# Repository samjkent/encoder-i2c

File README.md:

# EAW0J 128 Absolute Encoders and LEDs

128 position encoders with LEDs to display state

Encoder input is read using an MCP23017, and LED state is set using an HT16K33

# Large 

128 LEDs in a ring around a single encoder, with a circumference of roughly 6cm

# Small

4 encoders with 32 LEDs per encoder. Requires 2 MCP23017 to provide enough inputs for the encoders.

# Example Application

Combined with [samjkent/stm32f4-midi-brain](https://github.com/samjkent/stm32f4-midi-brain) to create a MIDI controller

# Note

The encoder footprint used in these schematics contains a mistake where pins 9 and 10 switched. Software for the current hardware takes this into account.

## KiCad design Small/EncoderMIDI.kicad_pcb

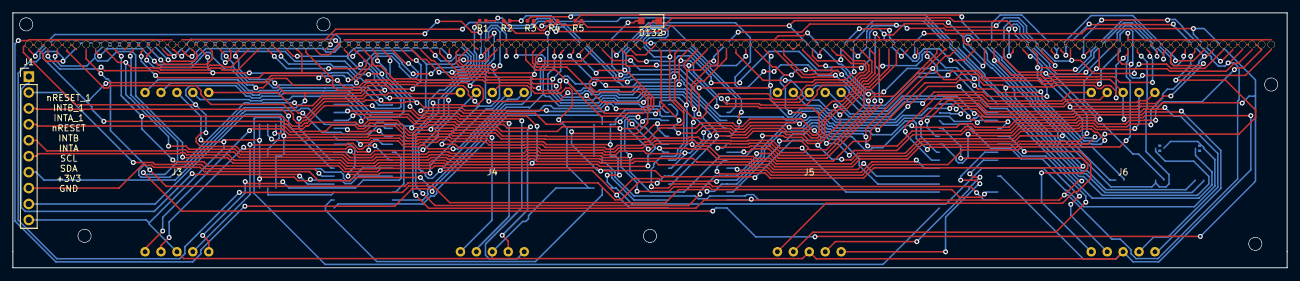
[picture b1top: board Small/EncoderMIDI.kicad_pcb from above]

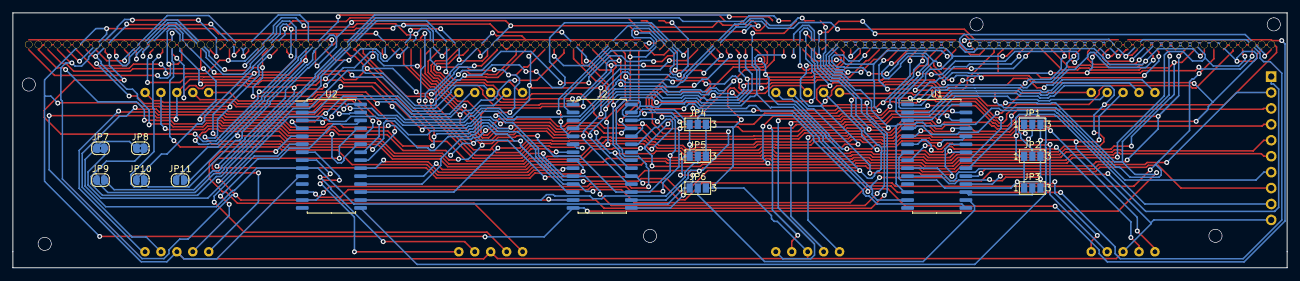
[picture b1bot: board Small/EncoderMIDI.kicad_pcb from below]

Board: 2 copper layers, 203.2 x 40.6 mm, 153 parts (14 on the bottom side), 58 nets.

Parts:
D1, D2, D3, D4, D5, D6, D7, D8, D9, D10, D11, D12, D13, D14, D15, D16, D17, D18, D19, D20, D21, D22, D23, D24, D25, D26, D27, D28, D29, D30, D31, D32, D34, D35, D36, D37, D38, D39, D40, D41, D42, D43, D44, D45, D46, D47, D48, D49, D50, D51, D52, D53, D54, D55, D56, D57, D58, D59, D60, D61, D62, D63, D64, D65, D67, D68, D69, D70, D71, D72, D73, D74, D75, D76, D77, D78, D79, D80, D81, D82, D83, D84, D85, D86, D87, D88, D89, D90, D91, D92, D93, D94, D95, D96, D97, D98, D100, D101, D102, D103, D104, D105, D106, D107, D108, D109, D110, D111, D112, D113, D114, D115, D116, D117, D118, D119, D120, D121, D122, D123, D124, D125, D126, D127, D128, D129, D130, D131: LED; LED_0603_1608Metric_FPDrillHoleEC
D132: D; D_SOD-123F
J1: Conn_01x10_Female; PinHeader_1x10_P2.54mm_Vertical
J2: HT16K33; SOIC-28W_7.5x17.9mm_P1.27mm
J3, J4, J5, J6: Conn_01x10_Female; EAW0J_FP
JP1, JP2, JP3, JP4, JP5, JP6: SolderJumper_3_Open; SolderJumper-3_P1.3mm_Open_Pad1.0x1.5mm_NumberLabels
JP7, JP8: SolderJumper_2_Bridged; SolderJumper-2_P1.3mm_Bridged2Bar_RoundedPad1.0x1.5mm
JP9, JP10, JP11: SolderJumper_2_Open; SolderJumper-2_P1.3mm_Open_RoundedPad1.0x1.5mm
R1, R2: 4.7K; R_0402_1005Metric
R3, R4, R5: 39K; R_0402_1005Metric
U1, U2: MCP23017-E_SO; SOIC-28W_7.5x17.9mm_P1.27mm

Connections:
+3V3: J1.9, J2.28, JP1.1, JP2.1, JP3.1, JP4.1, JP5.1, JP6.1, JP7.1, JP8.1, U1.9, U2.9
/Sheet5E07A93D/A0: JP2.2, U2.15
/Sheet5E07A93D/A0_1: JP4.2, U1.15
/Sheet5E07A93D/A1: JP5.2, U2.16
/Sheet5E07A93D/A1_1: JP6.2, U1.16
/Sheet5E07A93D/A2: JP1.2, U2.17
/Sheet5E07A93D/A2_1: JP3.2, U1.17
GND: J1.10, J2.1, J3.3, J3.8, J4.3, J4.8, J5.3, J5.8, J6.3, J6.8, JP1.3, JP2.3, JP3.3, JP4.3, JP5.3, JP6.3, U1.10, U2.10
INTA: J1.6, U2.20
INTA_1: J1.3, U1.20
INTB: J1.5, U2.19
INTB_1: J1.2, U1.19
unnamed: D132.2, J2.2
unnamed: J2.25, JP9.2
unnamed: J2.24, JP10.2
unnamed: J2.23, JP11.2
unnamed: D132.1, R3.1, R4.1, R5.1
unnamed: J3.1, U1.1
unnamed: J3.2, U1.2
unnamed: J3.4, U1.3
unnamed: J3.5, U1.4
unnamed: J3.6, U1.5
unnamed: J3.7, U1.6
unnamed: J3.9, U1.7
unnamed: J3.10, U1.8
unnamed: J4.1, U1.21
unnamed: J4.2, U1.22
unnamed: J4.4, U1.23
unnamed: J4.5, U1.24
unnamed: J4.6, U1.25
unnamed: J4.7, U1.26
unnamed: J4.9, U1.27
unnamed: J4.10, U1.28
unnamed: J5.1, U2.1
unnamed: J5.2, U2.2
unnamed: J5.4, U2.3
unnamed: J5.5, U2.4
unnamed: J5.6, U2.5
unnamed: J5.7, U2.6
unnamed: J5.9, U2.7
unnamed: J5.10, U2.8
unnamed: J6.1, U2.21
unnamed: J6.2, U2.22
unnamed: J6.4, U2.23
unnamed: J6.5, U2.24
unnamed: J6.6, U2.25
unnamed: J6.7, U2.26
unnamed: J6.9, U2.27
unnamed: J6.10, U2.28
unnamed: JP7.2, R1.1
unnamed: JP8.2, R2.1
unnamed: JP9.1, R3.2
unnamed: JP10.1, R4.2
unnamed: JP11.1, R5.2
SCL: J1.7, J2.26, R1.2, U1.12, U2.12
SDA: J1.8, J2.27, R2.2, U1.13, U2.13
nRESET: J1.4, U2.18
nRESET_1: J1.1, U1.18

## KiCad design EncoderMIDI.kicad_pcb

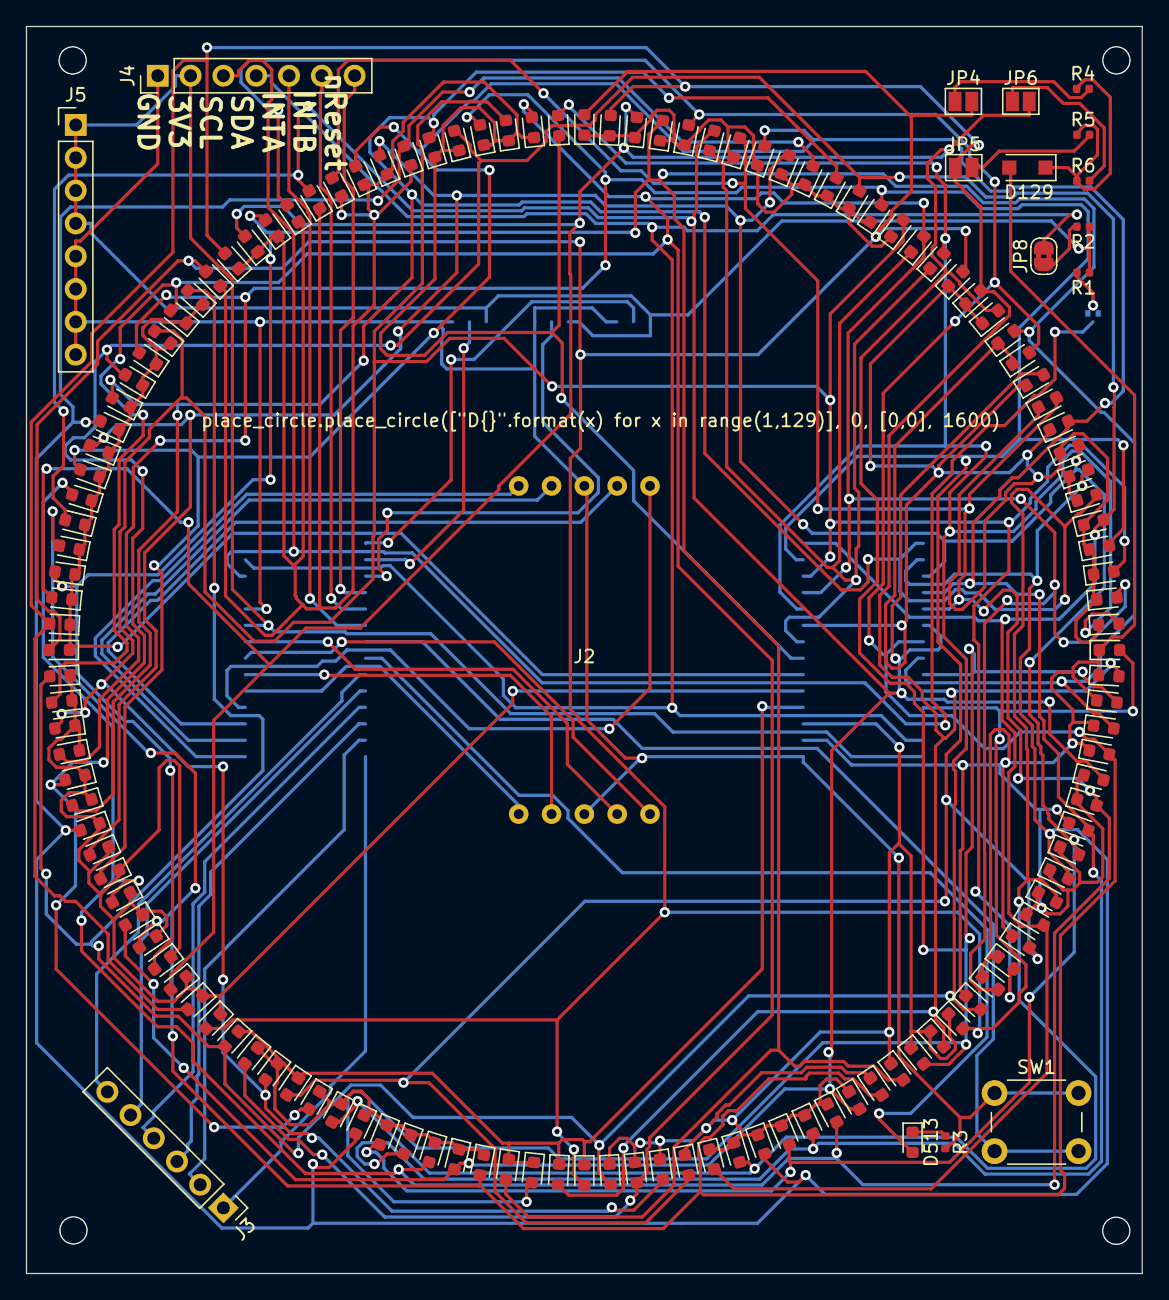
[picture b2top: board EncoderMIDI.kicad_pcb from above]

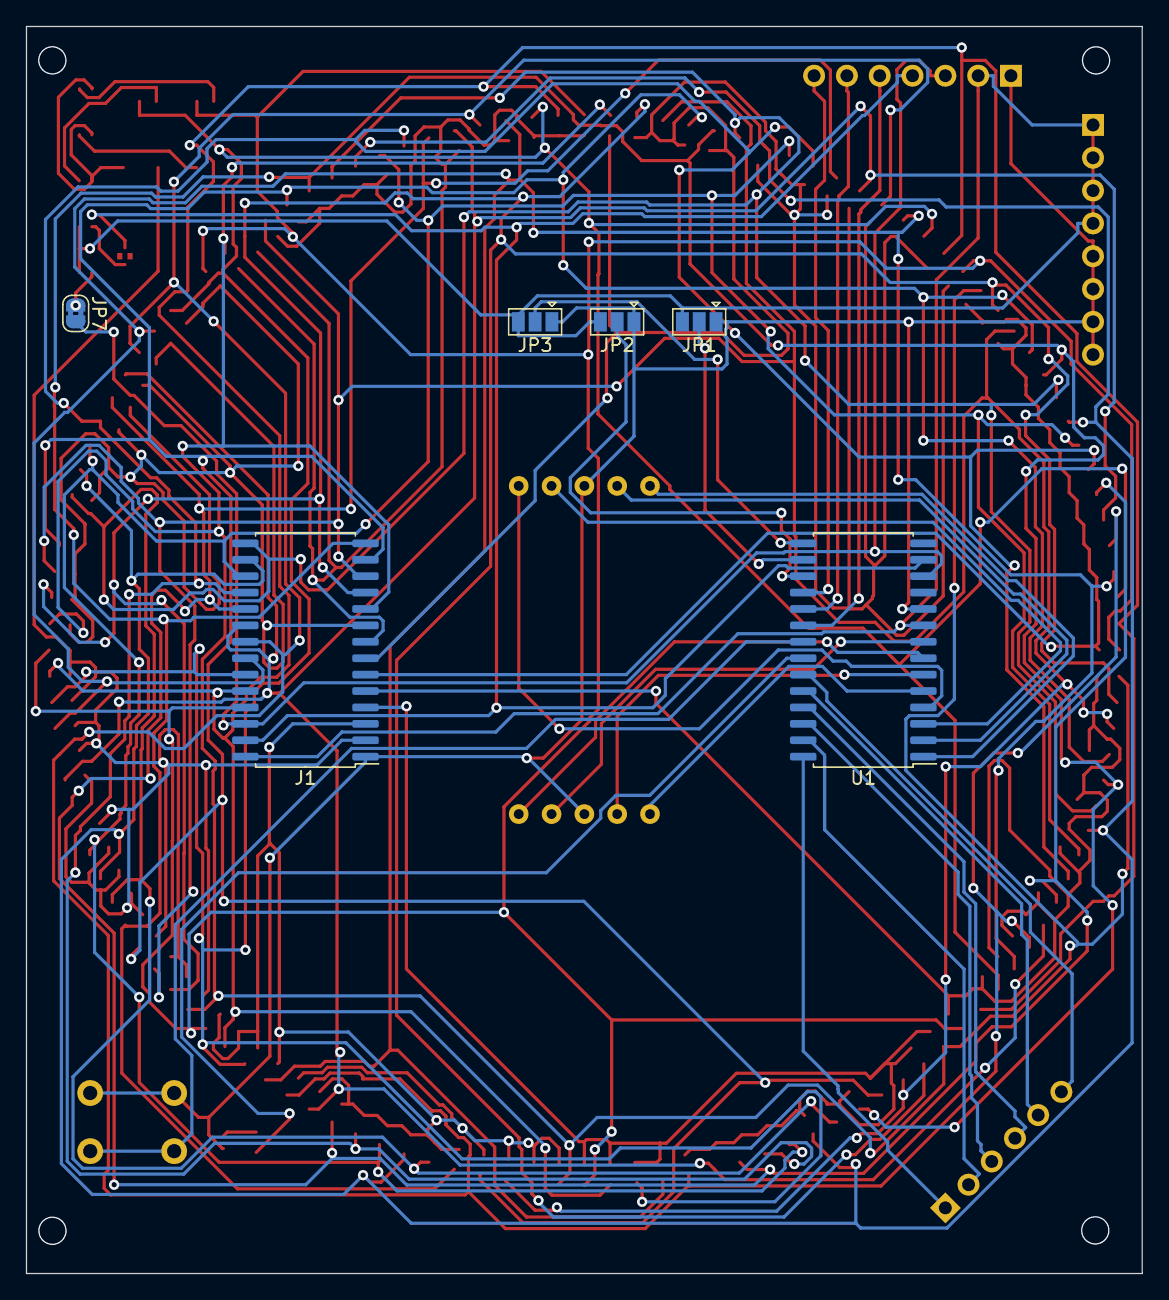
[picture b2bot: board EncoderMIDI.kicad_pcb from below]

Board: 2 copper layers, 86.4 x 96.5 mm, 151 parts (6 on the bottom side), 57 nets.

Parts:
D1, D2, D3, D4, D5, D6, D7, D8, D9, D10, D11, D12, D13, D14, D15, D16, D17, D18, D19, D20, D21, D22, D23, D24, D25, D26, D27, D28, D29, D30, D31, D32, D33, D34, D35, D36, D37, D38, D39, D40, D41, D42, D43, D44, D45, D46, D47, D48, D49, D50, D51, D52, D53, D54, D55, D56, D57, D58, D59, D60, D61, D62, D63, D64, D65, D66, D67, D68, D69, D70, D71, D72, D73, D74, D75, D76, D77, D78, D79, D80, D81, D82, D83, D84, D85, D86, D87, D88, D89, D90, D91, D92, D93, D94, D95, D96, D97, D98, D99, D100, D101, D102, D103, D104, D105, D106, D107, D108, D109, D110, D111, D112, D113, D114, D115, D116, D117, D118, D119, D120, D121, D122, D123, D124, D125, D126, D127, D128, D513: LED; LED_0603_1608Metric
D129: D; D_SOD-123F
J1: HT16K33; SOIC-28W_7.5x17.9mm_P1.27mm
J2: Conn_01x10_Female; EAW0J
J3: Conn_01x06_Female; PinHeader_1x06_P2.54mm_Vertical
J4: EXT_BUS; PinHeader_1x07_P2.54mm_Vertical
J5: Conn_01x08_Female; PinHeader_1x08_P2.54mm_Vertical
JP1: A1; SolderJumper-3_P1.3mm_Open_Pad1.0x1.5mm
JP2: A2; SolderJumper-3_P1.3mm_Open_Pad1.0x1.5mm
JP3: A0; SolderJumper-3_P1.3mm_Open_Pad1.0x1.5mm
JP4: A2; SolderJumper-2_P1.3mm_Open_Pad1.0x1.5mm
JP5: A1; SolderJumper-2_P1.3mm_Open_Pad1.0x1.5mm
JP6: A0; SolderJumper-2_P1.3mm_Open_Pad1.0x1.5mm
JP7, JP8: SolderJumper_2_Bridged; SolderJumper-2_P1.3mm_Bridged2Bar_RoundedPad1.0x1.5mm
R1, R2: 4.7K; R_0402_1005Metric
R3: R; R_0402_1005Metric
R4, R5, R6: 39K; R_0402_1005Metric
SW1: SW_Push; SW_PUSH_6mm
U1: MCP23017-E_SP; SOIC-28W_7.5x17.9mm_P1.27mm

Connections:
3V3: J1.28, J4.2, J5.1, J5.2, J5.3, J5.4, JP1.3, JP2.3, JP3.3, R1.1, R2.1, U1.9
/large_rotary/A0: JP3.2, U1.15
/large_rotary/A1: JP1.2, U1.16
/large_rotary/A2: JP2.2, U1.17
GND: J1.1, J2.3, J2.8, J4.1, J5.5, J5.6, J5.7, J5.8, JP1.1, JP2.1, JP3.1, R3.2, SW1.1, U1.10
INTA: J4.5, U1.20
INTB: J4.6, U1.19
unnamed: D1.1, D2.1, D3.1, D4.1, D5.1, D6.1, D7.1, D8.1, D9.1, D10.1, D11.1, D12.1, D13.1, D14.1, D15.1, D16.1, D129.2, J1.2
unnamed: D1.2, D17.2, D33.2, D49.2, D65.2, D81.2, D97.2, D113.2, J1.25, JP4.2
unnamed: D10.2, D26.2, D42.2, D58.2, D74.2, D90.2, D106.2, D122.2, J1.16
unnamed: D17.1, D18.1, D19.1, D20.1, D21.1, D22.1, D23.1, D24.1, D25.1, D26.1, D27.1, D28.1, D29.1, D30.1, D31.1, D32.1, J1.3
unnamed: D33.1, D34.1, D35.1, D36.1, D37.1, D38.1, D39.1, D40.1, D41.1, D42.1, D43.1, D44.1, D45.1, D46.1, D47.1, D48.1, J1.4
unnamed: D49.1, D50.1, D51.1, D52.1, D53.1, D54.1, D55.1, D56.1, D57.1, D58.1, D59.1, D60.1, D61.1, D62.1, D63.1, D64.1, J1.5
unnamed: D65.1, D66.1, D67.1, D68.1, D69.1, D70.1, D71.1, D72.1, D73.1, D74.1, D75.1, D76.1, D77.1, D78.1, D79.1, D80.1, J1.6
unnamed: D81.1, D82.1, D83.1, D84.1, D85.1, D86.1, D87.1, D88.1, D89.1, D90.1, D91.1, D92.1, D93.1, D94.1, D95.1, D96.1, J1.7
unnamed: D97.1, D98.1, D99.1, D100.1, D101.1, D102.1, D103.1, D104.1, D105.1, D106.1, D107.1, D108.1, D109.1, D110.1, D111.1, D112.1, J1.8
unnamed: D4.2, D20.2, D36.2, D52.2, D68.2, D84.2, D100.2, D116.2, J1.22
unnamed: D5.2, D21.2, D37.2, D53.2, D69.2, D85.2, D101.2, D117.2, J1.21
unnamed: D6.2, D22.2, D38.2, D54.2, D70.2, D86.2, D102.2, D118.2, J1.20
unnamed: D7.2, D23.2, D39.2, D55.2, D71.2, D87.2, D103.2, D119.2, J1.19
unnamed: D8.2, D24.2, D40.2, D56.2, D72.2, D88.2, D104.2, D120.2, J1.18
unnamed: D9.2, D25.2, D41.2, D57.2, D73.2, D89.2, D105.2, D121.2, J1.17
unnamed: D11.2, D27.2, D43.2, D59.2, D75.2, D91.2, D107.2, D123.2, J1.15
unnamed: D12.2, D28.2, D44.2, D60.2, D76.2, D92.2, D108.2, D124.2, J1.14
unnamed: D13.2, D29.2, D45.2, D61.2, D77.2, D93.2, D109.2, D125.2, J1.13
unnamed: D14.2, D30.2, D46.2, D62.2, D78.2, D94.2, D110.2, D126.2, J1.12
unnamed: D15.2, D31.2, D47.2, D63.2, D79.2, D95.2, D111.2, D127.2, J1.11
unnamed: D16.2, D32.2, D48.2, D64.2, D80.2, D96.2, D112.2, D128.2, J1.10
unnamed: D113.1, D114.1, D115.1, D116.1, D117.1, D118.1, D119.1, D120.1, D121.1, D122.1, D123.1, D124.1, D125.1, D126.1, D127.1, D128.1, J1.9
unnamed: D2.2, D18.2, D34.2, D50.2, D66.2, D82.2, D98.2, D114.2, J1.24, JP5.1
unnamed: D3.2, D19.2, D35.2, D51.2, D67.2, D83.2, D99.2, D115.2, J1.23, JP6.2
unnamed: D129.1, R4.1, R5.1, R6.1
unnamed: D513.1, R3.1
unnamed: D513.2, U1.22
unnamed: J2.1, U1.1
unnamed: J2.2, U1.2
unnamed: J2.4, U1.3
unnamed: J2.5, U1.4
unnamed: J2.6, U1.5
unnamed: J2.7, U1.6
unnamed: J2.9, U1.7
unnamed: J2.10, U1.8
unnamed: J3.1, U1.28
unnamed: J3.2, U1.27
unnamed: J3.3, U1.26
unnamed: J3.4, U1.25
unnamed: J3.5, U1.24
unnamed: J3.6, U1.23
unnamed: JP4.1, R4.2
unnamed: JP5.2, R5.2
unnamed: JP6.1, R6.2
unnamed: JP7.1, R1.2
unnamed: JP8.1, R2.2
unnamed: SW1.2, U1.21
SCL: J1.26, J4.3, JP7.2, U1.12
SDA: J1.27, J4.4, JP8.2, U1.13
nRESET: J4.7, U1.18

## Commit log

2021-01-13 add readme and render
2021-01-13 move to directory:
2021-01-13 add small
